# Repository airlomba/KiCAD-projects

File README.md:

# KiCAD-projects
KiCAD files fo some of my projects: schematics, layouts and netlists. Eventually, some libraries also.

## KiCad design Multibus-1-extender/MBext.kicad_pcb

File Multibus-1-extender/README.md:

KiCAD files for a <b>Multibus 1 Extender Card</b>.<br />

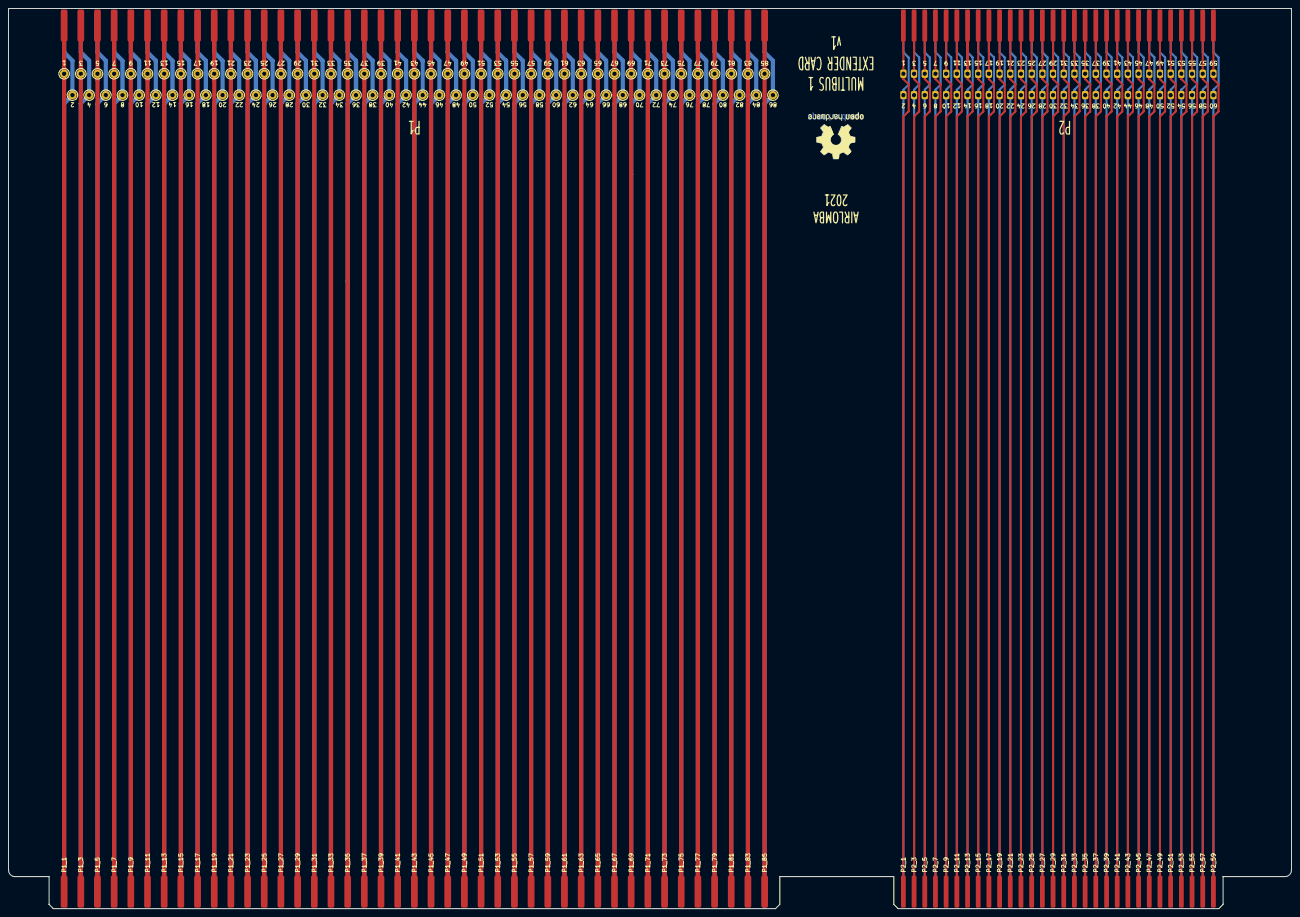
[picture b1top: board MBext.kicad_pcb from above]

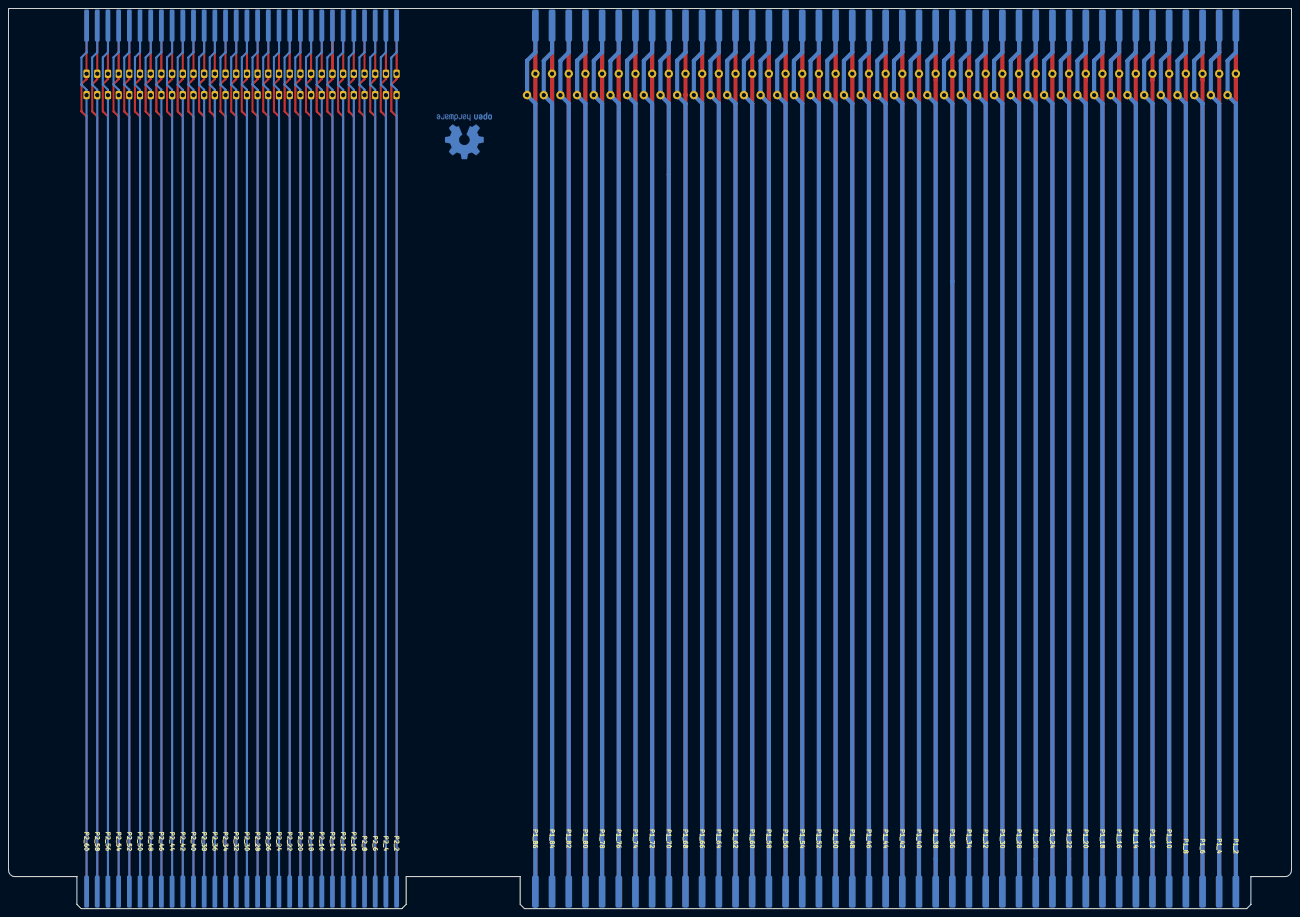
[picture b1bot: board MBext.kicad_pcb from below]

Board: 2 copper layers, 304.8 x 213.8 mm, 438 parts (146 on the bottom side), 146 nets.

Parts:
1, 2, 3, 4, 5, 6, 7, 8, 9, 10, 11, 12, 13, 14, 15, 16, 17, 18, 19, 20, 21, 22, 23, 24, 25, 26, 27, 28, 29, 30, 31, 32, 33, 34, 35, 36, 37, 38, 39, 40, 41, 42, 43, 44, 45, 46, 47, 48, 49, 50, 51, 52, 53, 54, 55, 56, 57, 58, 59, 60, 61, 62, 63, 64, 65, 66, 67, 68, 69, 70, 71, 72, 73, 74, 75, 76, 77, 78, 79, 80, 81, 82, 83, 84, 85, 86: Conn_01x01_Female; Pin_D1.0mm_L10.0mm
1#2, 2#2, 3#2, 4#2, 5#2, 6#2, 7#2, 8#2, 9#2, 10#2, 11#2, 12#2, 13#2, 14#2, 15#2, 16#2, 17#2, 18#2, 19#2, 20#2, 21#2, 22#2, 23#2, 24#2, 25#2, 26#2, 27#2, 28#2, 29#2, 30#2, 31#2, 32#2, 33#2, 34#2, 35#2, 36#2, 37#2, 38#2, 39#2, 40#2, 41#2, 42#2, 43#2, 44#2, 45#2, 46#2, 47#2, 48#2, 49#2, 50#2, 51#2, 52#2, 53#2, 54#2, 55#2, 56#2, 57#2, 58#2, 59#2, 60#2: Conn_01x01_Female; P2_TP
J87, J88, J89, J90, J91, J92, J93, J94, J95, J96, J97, J98, J99, J100, J101, J102, J103, J104, J105, J106, J107, J108, J109, J110, J111, J112, J113, J114, J115, J116, J117, J118, J119, J120, J121, J122, J123, J124, J125, J126, J127, J128, J129, J130, J131, J132, J133, J134, J135, J136, J137, J138, J139, J140, J141, J142, J143, J144, J145, J146, J147, J148, J149, J150, J151, J152, J153, J154, J155, J156, J157, J158, J159, J160, J161, J162, J163, J164, J165, J166, J167, J168, J169, J170, J171, J172: Conn_01x01_Female; P1
J235, J236, J237, J238, J239, J240, J241, J242, J243, J244, J245, J246, J247, J248, J249, J250, J251, J252, J253, J254, J255, J256, J257, J258, J259, J260, J261, J262, J263, J265, J266, J267, J268, J269, J270, J271, J272, J273, J274, J275, J276, J277, J278, J279, J280, J281, J282, J283, J284, J285, J286, J287, J288, J289, J290, J291, J292, J293, J294: Conn_01x01_Female; P2
P1_1, P1_2, P1_3, P1_4, P1_5, P1_6, P1_7, P1_8, P1_9, P1_10, P1_11, P1_12, P1_13, P1_14, P1_15, P1_16, P1_17, P1_18, P1_19, P1_20, P1_21, P1_22, P1_23, P1_24, P1_25, P1_26, P1_27, P1_28, P1_29, P1_30, P1_31, P1_32, P1_33, P1_34, P1_35, P1_36, P1_37, P1_38, P1_39, P1_40, P1_41, P1_42, P1_43, P1_44, P1_45, P1_46, P1_47, P1_48, P1_49, P1_50, P1_51, P1_52, P1_53, P1_54, P1_55, P1_56, P1_57, P1_58, P1_59, P1_60, P1_61, P1_62, P1_63, P1_64, P1_65, P1_66, P1_67, P1_68, P1_69, P1_70, P1_71, P1_72, P1_73, P1_74, P1_75, P1_76, P1_77, P1_78, P1_79, P1_80, P1_81, P1_82, P1_83, P1_84, P1_85, P1_86: Conn_01x01_Male; P1
P2_1: Conn_01x01_Female; P2
P2_1#2, P2_2, P2_3, P2_4, P2_5, P2_6, P2_7, P2_8, P2_9, P2_10, P2_11, P2_12, P2_13, P2_14, P2_15, P2_16, P2_17, P2_18, P2_19, P2_20, P2_21, P2_22, P2_23, P2_24, P2_25, P2_26, P2_27, P2_28, P2_29, P2_30, P2_31, P2_32, P2_33, P2_34, P2_35, P2_36, P2_37, P2_38, P2_39, P2_40, P2_41, P2_42, P2_43, P2_44, P2_45, P2_46, P2_47, P2_48, P2_49, P2_50, P2_51, P2_52, P2_53, P2_54, P2_55, P2_56, P2_57, P2_58, P2_59, P2_60: Conn_01x01_Male; P2

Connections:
unnamed: 1.1, J87.1, P1_1.1
unnamed: 3.1, J88.1, P1_3.1
unnamed: 5.1, J89.1, P1_5.1
unnamed: 7.1, J90.1, P1_7.1
unnamed: 9.1, J91.1, P1_9.1
unnamed: 11.1, J92.1, P1_11.1
unnamed: 13.1, J93.1, P1_13.1
unnamed: 15.1, J94.1, P1_15.1
unnamed: 17.1, J95.1, P1_17.1
unnamed: 19.1, J96.1, P1_19.1
unnamed: 21.1, J97.1, P1_21.1
unnamed: 23.1, J98.1, P1_23.1
unnamed: 25.1, J99.1, P1_25.1
unnamed: 27.1, J100.1, P1_27.1
unnamed: 29.1, J101.1, P1_29.1
unnamed: 31.1, J102.1, P1_31.1
unnamed: 33.1, J103.1, P1_33.1
unnamed: 35.1, J104.1, P1_35.1
unnamed: 37.1, J105.1, P1_37.1
unnamed: 39.1, J106.1, P1_39.1
unnamed: 41.1, J107.1, P1_41.1
unnamed: 43.1, J108.1, P1_43.1
unnamed: 45.1, J109.1, P1_45.1
unnamed: 47.1, J110.1, P1_47.1
unnamed: 49.1, J111.1, P1_49.1
unnamed: 51.1, J112.1, P1_51.1
unnamed: 53.1, J113.1, P1_53.1
unnamed: 55.1, J114.1, P1_55.1
unnamed: 57.1, J115.1, P1_57.1
unnamed: 59.1, J116.1, P1_59.1
unnamed: 61.1, J117.1, P1_61.1
unnamed: 63.1, J118.1, P1_63.1
unnamed: 65.1, J119.1, P1_65.1
unnamed: 67.1, J120.1, P1_67.1
unnamed: 69.1, J121.1, P1_69.1
unnamed: 71.1, J122.1, P1_71.1
unnamed: 73.1, J123.1, P1_73.1
unnamed: 75.1, J124.1, P1_75.1
unnamed: 77.1, J125.1, P1_77.1
unnamed: 79.1, J126.1, P1_79.1
unnamed: 81.1, J127.1, P1_81.1
unnamed: 83.1, J128.1, P1_83.1
unnamed: 85.1, J129.1, P1_85.1
unnamed: 2.1, J130.1, P1_2.1
unnamed: 4.1, J131.1, P1_4.1
unnamed: 6.1, J132.1, P1_6.1
unnamed: 8.1, J133.1, P1_8.1
unnamed: 10.1, J134.1, P1_10.1
unnamed: 12.1, J135.1, P1_12.1
unnamed: 14.1, J136.1, P1_14.1
unnamed: 16.1, J137.1, P1_16.1
unnamed: 18.1, J138.1, P1_18.1
unnamed: 20.1, J139.1, P1_20.1
unnamed: 22.1, J140.1, P1_22.1
unnamed: 24.1, J141.1, P1_24.1
unnamed: 26.1, J142.1, P1_26.1
unnamed: 28.1, J143.1, P1_28.1
unnamed: 30.1, J144.1, P1_30.1
unnamed: 32.1, J145.1, P1_32.1
unnamed: 34.1, J146.1, P1_34.1
unnamed: 36.1, J147.1, P1_36.1
unnamed: 38.1, J148.1, P1_38.1
unnamed: 40.1, J149.1, P1_40.1
unnamed: 42.1, J150.1, P1_42.1
unnamed: 44.1, J151.1, P1_44.1
unnamed: 46.1, J152.1, P1_46.1
unnamed: 48.1, J153.1, P1_48.1
unnamed: 50.1, J154.1, P1_50.1
unnamed: 52.1, J155.1, P1_52.1
unnamed: 54.1, J156.1, P1_54.1
unnamed: 56.1, J157.1, P1_56.1
unnamed: 58.1, J158.1, P1_58.1
unnamed: 60.1, J159.1, P1_60.1
unnamed: 62.1, J160.1, P1_62.1
unnamed: 64.1, J161.1, P1_64.1
unnamed: 66.1, J162.1, P1_66.1
unnamed: 68.1, J163.1, P1_68.1
unnamed: 70.1, J164.1, P1_70.1
unnamed: 72.1, J165.1, P1_72.1
unnamed: 74.1, J166.1, P1_74.1
unnamed: 76.1, J167.1, P1_76.1
unnamed: 78.1, J168.1, P1_78.1
unnamed: 80.1, J169.1, P1_80.1
unnamed: 82.1, J170.1, P1_82.1
unnamed: 84.1, J171.1, P1_84.1
unnamed: 86.1, J172.1, P1_86.1
unnamed: 1#2.1, P2_1.1, P2_1#2.1
unnamed: 3#2.1, J235.1, P2_3.1
unnamed: 5#2.1, J236.1, P2_5.1
unnamed: 7#2.1, J237.1, P2_7.1
unnamed: 9#2.1, J238.1, P2_9.1
unnamed: 11#2.1, J239.1, P2_11.1
unnamed: 13#2.1, J240.1, P2_13.1
unnamed: 15#2.1, J241.1, P2_15.1
unnamed: 17#2.1, J242.1, P2_17.1
unnamed: 19#2.1, J243.1, P2_19.1
unnamed: 21#2.1, J244.1, P2_21.1
unnamed: 23#2.1, J245.1, P2_23.1
unnamed: 25#2.1, J246.1, P2_25.1
unnamed: 27#2.1, J247.1, P2_27.1
unnamed: 29#2.1, J248.1, P2_29.1
unnamed: 31#2.1, J249.1, P2_31.1
unnamed: 33#2.1, J250.1, P2_33.1
unnamed: 35#2.1, J251.1, P2_35.1
unnamed: 37#2.1, J252.1, P2_37.1
unnamed: 39#2.1, J253.1, P2_39.1
unnamed: 41#2.1, J254.1, P2_41.1
unnamed: 43#2.1, J255.1, P2_43.1
unnamed: 45#2.1, J256.1, P2_45.1
unnamed: 47#2.1, J257.1, P2_47.1
unnamed: 49#2.1, J258.1, P2_49.1
unnamed: 51#2.1, J259.1, P2_51.1
unnamed: 53#2.1, J260.1, P2_53.1
unnamed: 55#2.1, J261.1, P2_55.1
unnamed: 57#2.1, J262.1, P2_57.1
unnamed: 59#2.1, J263.1, P2_59.1
unnamed: 2#2.1, J265.1, P2_2.1
unnamed: 4#2.1, J266.1, P2_4.1
unnamed: 6#2.1, J267.1, P2_6.1
unnamed: 8#2.1, J268.1, P2_8.1
unnamed: 10#2.1, J269.1, P2_10.1
unnamed: 12#2.1, J270.1, P2_12.1
unnamed: 14#2.1, J271.1, P2_14.1
unnamed: 16#2.1, J272.1, P2_16.1
unnamed: 18#2.1, J273.1, P2_18.1
unnamed: 20#2.1, J274.1, P2_20.1
unnamed: 22#2.1, J275.1, P2_22.1
unnamed: 24#2.1, J276.1, P2_24.1
unnamed: 26#2.1, J277.1, P2_26.1
unnamed: 28#2.1, J278.1, P2_28.1
unnamed: 30#2.1, J279.1, P2_30.1
unnamed: 32#2.1, J280.1, P2_32.1
unnamed: 34#2.1, J281.1, P2_34.1
unnamed: 36#2.1, J282.1, P2_36.1
unnamed: 38#2.1, J283.1, P2_38.1
unnamed: 40#2.1, J284.1, P2_40.1
unnamed: 42#2.1, J285.1, P2_42.1
unnamed: 44#2.1, J286.1, P2_44.1
unnamed: 46#2.1, J287.1, P2_46.1
unnamed: 48#2.1, J288.1, P2_48.1
unnamed: 50#2.1, J289.1, P2_50.1
unnamed: 52#2.1, J290.1, P2_52.1
unnamed: 54#2.1, J291.1, P2_54.1
unnamed: 56#2.1, J292.1, P2_56.1
unnamed: 58#2.1, J293.1, P2_58.1
unnamed: 60#2.1, J294.1, P2_60.1

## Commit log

2021-08-30 Create lala
